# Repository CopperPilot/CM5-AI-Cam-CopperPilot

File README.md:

# CM5 AI Camera Carrier Board: 6-Layer Edge AI Vision Platform

An ultra-compact, high-density, 6-layer carrier board designed for the **Raspberry Pi Compute Module 5 (CM5)**, purpose-built for embedded computer vision, edge AI inference, autonomous robotics, and smart camera applications. Engineered in an exact 55.0 mm × 40.0 mm form factor matching the CM5 module dimensions, the board provides dedicated low-noise power rails, controlled-impedance differential routing (**100 Ω for MIPI and HDMI, 90 Ω for USB**), onboard common-mode filtering, high-speed peripheral multiplexing, and standard 40-pin Raspberry Pi GPIO expansion.

---

## 3D Hardware Presentation

| Top Isometric View | Bottom Mezzanine View |
|:---:|:---:|
|  |  |

| Full System Isometric | Top Routing (F.Cu) |
|:---:|:---:|
|  |  |

---

## System Architecture

```
                    +-------------------------------------------------------+
                    |                      Power Entry                      |
                    | USB-C (Type_C1) w/ 5.1k CC (R2, R3) OR 40-Pin PI1 Header
                    |                             |                         |
                    |               MPS MP1658 3.3V / 3A Buck (U5)          |
                    |                             |                         |
                    |     +-----------------------+-------------------+     |
                    |     |                       |                   |     |
                    | RT9193-2.8V (U1)    RT9193-1.8V (U2)    RT9013-1.2V (U3)
                    +-----+-----------------------+-------------------+-----+
                          |                       |                   |
                     CAM_2V8 Rail            CAM_1V8 Rail        CAM_1V2 Rail
                          |                       |                   |
+-------------------------v-----------------------v-------------------v-----+
|                         Camera Imaging Subsystem                          |
| 30-Pin Sony IMX219 Autofocus Camera Connector (J1)                        |
| 3x 1210 High-Frequency Common-Mode Chokes (L1, L2, L3)                    |
| 2-Lane MIPI CSI-2 (100 Ω Differential, HighSpeed_100R, 0.127 mm Width)    |
+---------------------------------------------+-----------------------------+
                                              |
                          Mezzanine DF40C     | MIPI CSI-2 (100 Ω Diff)
                          Mezzanine DF40C     | (High-Speed Imaging)
+---------------------------------------------v-----------------------------+
|                     Raspberry Pi Compute Module 5 (Module1)               |
| Dual 100-Pin Mezzanine Connectors (Hirose DF40C-100DS-0.4V)                |
| Broadcom BCM2712 Quad-Core Cortex-A76 @ 2.4 GHz, LPDDR4X SDRAM, PCIe 2.0  |
+------+--------------+---------------+---------------+--------------+------+
       | 100 Ω        | 100 Ω         | 90 Ω          | 50 Ω         |
  HDMI | Diff     DSI | Diff      USB | Diff     SDIO | SE      GPIO |
+------v-------+ +----v---------+ +---v---------+ +---v--------+ +---v------+
| Mini-HDMI-C  | | 15-Pin DSI   | | FSUSB42UMX  | | MicroSD    | | 40-Pin   |
| (HDMI1) w/   | | Display FPC  | | Mux (U6) to | | Slot (TF1) | | GPIO     |
| STMPS2171    | | Connector    | | USB-A (J2,  | | w/ Power   | | Header   |
| Switch (U4)  | | (DSI1, 3.3V) | | U8) & USB-C | | Switch(U7) | | (PI1)    |
+--------------+ +--------------+ +-------------+ +------------+ +----------+
```

---

## Reference Design Attribution & Technical Improvements

This design was developed using the architecture and schematic concepts of the **Waveshare CM4 / CM5 Nano Base Board (C)** as an engineering reference. Our team conducted a thorough hardware design review and implemented major electrical, signal integrity, DFM, and manufacturing improvements to deliver a validated, production-ready edge AI camera carrier.

### Summary of Key Engineering Improvements

| Domain | Baseline Reference Limitation | Implemented Engineering Improvement | Benefit / Impact |
|---|---|---|---|
| **Power Regulation** | Faulty feedback divider and mismatched LCSC part (`C25916` 6.49 kΩ) on 3.3V buck regulator `U5` (`MP1658GTF-Z`, `C2960187`); `C21` snubber capacitor assigned 12 pF (`C1547`). | Configured feedback divider with precision 61.9 kΩ ±1% (`R20`, `C25803`) and 20.0 kΩ ±1% (`R21`, `C25765`) resistors for exact **3.305 V** output ($V_{REF}=0.807\text{ V}$); verified 0.1 µF bootstrap (`C24`) and 10 Ω + 330 pF (`R16` + `C21`, `C1534`) SW snubber. | Eliminates catastrophic overvoltage/undervoltage risk on `/PWR_3V3` and damps high-frequency switching ring. |
| **Camera Power & Clock** | `U3` 1.2V camera core LDO assigned a 3.3V LCSC part (`C7434207`); `U1` 2.8V LDO assigned an invalid LCSC code; `C20` on 24 MHz `/MCLK` set to 0.1 µF (`fc = 72.3 kHz`), attenuating the sensor clock. | Assigned verified Richtek LDOs (`U1` 2.8V `C15075`, `U2` 1.8V `C27416`, `U3` 1.2V `C47773`) and restored `C20` to **10 pF (`C32949`)** with `R10 = 22 Ω` (`fc = 723 MHz`). | Protects the 1.2V Sony IMX219 core from 3.3V overvoltage and preserves clean 24 MHz CMOS clock integrity. |
| **Differential Impedance (`100 Ω` vs `90 Ω`)** | Unassigned netclasses in `.kicad_pro` (`netclass_patterns: []`) and documentation conflating MIPI CSI-2, DSI, HDMI TMDS, and USB into a single 90 Ω class with 0.150 mm default trace widths. | Separated and assigned **`HighSpeed_100R` (100 Ω for MIPI CSI-2, MIPI DSI, and HDMI TMDS: `W = 0.127 mm, S = 0.150 mm`)** and **`HighSpeed_90R` (90 Ω for USB 2.0: `W = 0.180 mm, S = 0.150 mm`)** across `.kicad_pro`, `.kicad_pcb`, and `.kicad_dru`. | Matches official Raspberry Pi CM5/CM4, MIPI D-PHY, HDMI 1.4b/2.0 (100 Ω), and USB 2.0 Hi-Speed (90 Ω) specifications on JLCPCB's impedance calculator. |
| **USB Architecture** | Package suffix mismatch on `U6` (`FSUSB42MX` MSOP-10 vs `FSUSB42UMX` UQFN-10) and unverified VBUS switch documentation. | Standardized `U6` to `FSUSB42UMX` (`C11145`, `UQFN-10_1.4x1.8mm_P0.4mm`) with `STMPS2171STR` (`U8`) providing dedicated 5V load switching for USB-A host port `J2`. | Enables reliable USB 2.0 routing between USB-C (`rpiboot` device mode) and vertical USB-A host peripheral port. |
| **Display Connector Parity** | `DSI1` 15-pin FPC connector symbol included legacy unrouted pin `SH` with no matching pad name on footprint `Molex_200528-0150`. | Synchronized `CM5:DSI_15P` symbol with the 15-circuit footprint so `kicad-cli pcb drc --schematic-parity` passes with zero net conflicts. | Eliminates schematic-to-PCB netlist parity errors. |
| **DFM & Custom Rules** | Custom DRC rules in `.kicad_dru` lacked explicit Decision ID traceability and controlled-impedance width constraints. | Annotated all custom rules (`DEC-001` through `DEC-005`) and added explicit `HighSpeed_100R_Impedance_Width` (`0.127 mm`) and `HighSpeed_90R_Impedance_Width` (`0.180 mm`) DRC constraints. | Enforces trace width and clearance compliance automatically during `kicad-cli pcb drc`. |
| **Turnkey PCBA Sourcing** | DNP strap resistors (`R31`, `R32`, `R33` for `WL_nDisable`, `BT_nDisable`, `USB_OTG_ID`) erroneously included in BOM/CPL; mismatched LCSC codes on `HDMI1` and `L1–L3`. | Excluded DNP straps `R31–R33` (`--exclude-dnp`) so Wi-Fi/Bluetooth stay enabled; assigned verified LCSC parts for `HDMI1` (`C424662`) and 1.2×1.0 mm chokes `L1–L3` (`C110443`); consolidated `0.1uF` (`C1525`) BOM rows. | Ready for automated turnkey fabrication and double-sided SMT assembly (87 populated parts across 42 BOM lines). |
| **Automated Testing** | No automated verification of differential netclasses, controlled-impedance trace widths, or critical BOM LCSC mappings. | Expanded the automated PyTest verification suite (`tests/test_pcb.py`) to **29 assertion tests** alongside the 11-stage acceptance runner (`review/verify.sh`). | Continuously verifies physical dimensions, stackup, `100 Ω` / `90 Ω` differential netclasses and trace widths, DRC/ERC parity, and BOM/CPL integrity. |

---

## Hardware Specifications

- **Form Factor & Dimensions:** 55.0 mm × 40.0 mm matching the Raspberry Pi Compute Module mechanical standard, with 3.0 mm corner radii.
- **Compute Module Mezzanine:** Dual Hirose DF40C-100DS-0.4V(51) 100-pin connectors (`Module1`, `C597931`) with 0.40 mm pitch providing high-speed interconnects for MIPI CSI-2, MIPI DSI, HDMI TMDS, USB 2.0, SDIO, and GPIO.
- **Power Subsystem:**
  - **Main Input:** 5.0 V DC via USB Type-C receptacle (`Type_C1`, GCT USB4105-GF-A, `C3020560`) or via 40-pin GPIO expansion header (`PI1`). Recommended power supply: 5V / 3A minimum.
  - **Type-C Configuration:** Dual 5.1 kΩ ±1% CC pull-down resistors (`R2`, `R3`, `C25905`) for standard 5V/3A USB Type-C source negotiation.
  - **3.3 V System Rail (`/PWR_3V3`):** Monolithic Power Systems `MP1658GTF-Z` synchronous buck converter (`U5`, SOT-563, `C2960187`) delivering up to 3.0 A continuous output current (`R20 = 61.9 kΩ C25803`, `R21 = 20.0 kΩ C25765` for 3.305 V nominal output), filtered by a 4.7 µH shielded power inductor (`L7`, `C840574`) and dual 22 µF 0805 ceramic output capacitors (`C25`, `C26`).
  - **Low-Noise Camera Power Tree:**
    - `CAM_2V8` (`/2V8`): 2.8 V analog rail via Richtek `RT9193-28GB` LDO (`U1`, `C15075`) with ferrite bead input filter (`FB1`, 120 Ω `C50843`).
    - `CAM_1V8` (`/1V8`): 1.8 V digital I/O and oscillator rail via Richtek `RT9193-18GB` LDO (`U2`, `C27416`).
    - `CAM_1V2` (`/1V2`): 1.2 V core logic rail via Richtek `RT9013-12` LDO (`U3`, `C47773`).
- **Camera Imaging Subsystem:**
  - 30-pin 0.4 mm pitch board-to-board / FPC receptacle (`J1`, Hirose `DF37NB-30DS-0.4V(75)`, `C6539772`) designed for Sony IMX219-D160 camera modules.
  - Three 1.2 × 1.0 mm 90 Ω common-mode chokes (`L1`, `L2`, `L3`, `MCF1210BF2-900T01`, `C110443`) placed on MIPI CSI-2 clock and data lanes for high-frequency common-mode noise suppression.
  - Controlled **100 Ω differential impedance** (`HighSpeed_100R`, `W = 0.127 mm, S = 0.150 mm`) on MIPI CSI-2 lanes (`/CAM0_*` and `/CSI_*`).
  - 24.0 MHz CMOS crystal oscillator (`X1`, 3.2 × 2.5 mm, `C717686`) with 22 Ω series damping resistor (`R10`) and 10 pF edge-rate filter capacitor (`C20`, `C32949`, $f_c = 723\text{ MHz}$).
- **Video & Display Interfaces:**
  - **Mini-HDMI Type-C:** Molex 47151-0001 connector (`HDMI1`, `C424662`) with dedicated 5 V power distribution switch (`U4`, `STMPS2171STR`, `C157437`), hot-plug detection, and controlled **100 Ω differential impedance** (`HighSpeed_100R`, `W = 0.127 mm, S = 0.150 mm`) on TMDS clock and data pairs (`/HDMI0_CLK_P/N`, `/HDMI0_TX0..2_P/N`).
  - **MIPI DSI Display:** 15-pin 1.0 mm pitch Molex 200528-0150 horizontal FPC connector (`DSI1`, `C2914074`) powered from `/PWR_3V3` with controlled **100 Ω differential impedance** (`HighSpeed_100R`, `W = 0.127 mm, S = 0.150 mm`) on DSI clock and data lanes (`/DSI1_CLK_P/N`, `/DSI1_D0..1_P/N`).
- **Storage & USB Communication:**
  - **MicroSD Card:** Push-push MicroSD card socket (`TF1`, `C91145`) with dedicated `STMPS2171STR` 3.3 V load switch (`U7`, `C157437`) controlled by `/SD_PWREN`.
  - **USB 2.0 Architecture:** Vertical USB 2.0 Type-A host port (`J2`, Molex 67298-4090, `C698207`) with `STMPS2171STR` 5 V VBUS switch (`U8`, `C157437`) and USB Type-C peripheral port (`Type_C1`) multiplexed through an onsemi `FSUSB42UMX` high-speed USB 2.0 switch (`U6`, `C11145`), routed at controlled **90 Ω differential impedance** (`HighSpeed_90R`, `W = 0.180 mm, S = 0.150 mm`).
- **User Interface & Indicators:**
  - Tactile user push-button (`Key1`, `C318884`) connected to `GPIO21` with a 10 kΩ pull-up (`R11`) to `/PWR_3V3`.
  - Status LEDs: 0603 Red 3.3V Power LED (`L5`, `C2286`) and Green Activity LED (`L6`, `C72043`).

---

## Getting Started & Operating Guide

### 1. Mounting the Compute Module 5
1. Align the Compute Module 5 over the dual Hirose DF40C mezzanine connectors (`Module1`) on the bottom side (`B.Cu`).
2. Gently apply uniform downward pressure across the connectors until both 100-pin receptacles click firmly into place.

### 2. Powering the Carrier Board
- **Primary Power (USB-C):** Connect a regulated 5.0 V / 3.0 A USB-C power supply to receptacle `Type_C1`. The onboard CC termination resistors (`R2`, `R3`) negotiate standard 5V operation from USB Power Delivery sources.
- **Alternative Power (GPIO Header):** Connect a regulated 5.0 V DC supply to Pins 2/4 (`5V`) and Pin 6 (`GND`) of the 40-pin header (`PI1`). Do not connect an external 5V supply to `PI1` simultaneously with a host PC on `Type_C1`.
- **Power Indicator:** The onboard red LED (`L5`) illuminates immediately when the regulated 3.3V system rail (`/PWR_3V3`) is active.

### 3. Flashing Compute Module 5 eMMC
For CM5 modules equipped with onboard eMMC:
1. Pull both `/PI_BOOT` (`H4` Pin 1) and `/USB_SEL` (`H4` Pin 3) low to `GND` (`H4` Pin 2) so the BCM2712 processor enters USB `rpiboot` mode and the `FSUSB42UMX` multiplexer (`U6`) selects the USB Type-C port (`Type_C1`).
2. Connect the carrier board to a host PC using the USB Type-C port (`Type_C1`) and run `rpiboot`:
   ```bash
   rpiboot
   ```
3. The CM5 eMMC storage will mount as a mass-storage device on your computer for OS imaging.

### 4. Camera Configuration (Sony IMX219 / MIPI CSI-2)
1. Attach the 30-pin Sony IMX219-D160 camera module to connector `J1`.
2. In Raspberry Pi OS, configure the camera overlay by editing `/boot/firmware/config.txt`:
   ```ini
   # Enable Sony IMX219 Camera Sensor
   dtoverlay=imx219
   ```
3. Reboot and verify camera enumeration using `rpicam-apps`:
   ```bash
   rpicam-hello --list-cameras
   rpicam-hello -t 5000
   ```

### 5. Display Configuration
- **Mini-HDMI (`HDMI1`):** Plug a standard Mini-HDMI to HDMI cable into `HDMI1`. Video output is automatically detected via EDID / HPD.
- **MIPI DSI Display (`DSI1`):** Connect a 15-pin 1.0 mm pitch DSI display ribbon cable to `DSI1` and enable the matching DSI overlay in `/boot/firmware/config.txt` (e.g., `dtoverlay=vc4-kms-dsi-7inch`).

### 6. User Button & GPIO Header
- The tactile push-button (`Key1`) is wired to `GPIO21` with a 10 kΩ pull-up (`R11`) to `/PWR_3V3`. Pressing the button pulls `GPIO21` low.
- The 40-pin GPIO header (`PI1`) follows the standard Raspberry Pi 40-pin pinout.

---

## 6-Layer PCB Stackup & Impedance Control

The board `.kicad_pcb` stackup is synchronized with the **JLCPCB JLC06161H-7628** 6-layer controlled-impedance stackup (1.6 mm nominal thickness, with cross-compatibility verified against **JLC06161H-3313**):

| Layer | Type | Copper Weight | Thickness | Physical Allocation in `.kicad_pcb` |
|---|---|:---:|:---:|---|
| **1. F.Cu** | Signal | 1.0 oz (35 µm) | 0.0350 mm | Top SMT components, high-speed microstrip escapes, camera chokes (`L1–L3`), buck converter (`U5`) |
| *Dielectric 1* | Prepreg (7628) | — | 0.2104 mm | FR-4 ($\varepsilon_r = 4.6$; `0.0994 mm` $\varepsilon_r = 4.05$ on `JLC06161H-3313`) |
| **2. In1.Cu** | Plane / Signal | 0.5 oz (15.2 µm) | 0.0152 mm | Primary `GND` reference plane (`zone GND`) and inner escape routing |
| *Dielectric 2* | Core | — | 0.4000 mm | FR-4 Core ($\varepsilon_r = 4.6$; `0.5500 mm` on `JLC06161H-3313`) |
| **3. In2.Cu** | Signal | 0.5 oz (15.2 µm) | 0.0152 mm | Inner high-speed signal routing (`HDMI0`, `DSI1`, peripheral signals) |
| *Dielectric 3* | Prepreg (7628) | — | 0.2104 mm | FR-4 ($\varepsilon_r = 4.6$; `0.0994 mm` $\varepsilon_r = 4.05$ on `JLC06161H-3313`) |
| **4. In3.Cu** | Power / Signal | 0.5 oz (15.2 µm) | 0.0152 mm | Internal power distribution zones (`/PWR_3V3`, `/CM5_5V`) and inner signal routing |
| *Dielectric 4* | Core | — | 0.4000 mm | FR-4 Core ($\varepsilon_r = 4.6$; `0.5500 mm` on `JLC06161H-3313`) |
| **5. In4.Cu** | Plane / Signal | 0.5 oz (15.2 µm) | 0.0152 mm | Secondary `GND` reference plane (`zone GND`) and high-speed routing |
| *Dielectric 5* | Prepreg (7628) | — | 0.2104 mm | FR-4 ($\varepsilon_r = 4.6$; `0.0994 mm` $\varepsilon_r = 4.05$ on `JLC06161H-3313`) |
| **6. B.Cu** | Signal | 1.0 oz (35 µm) | 0.0350 mm | Bottom mezzanine (`Module1`), camera LDOs (`U1–U3`), USB mux (`U6`), power switches (`U4, U7, U8`) |

### Controlled Impedance Targets (**100 Ω for MIPI and HDMI, 90 Ω for USB**)

The project `.kicad_pro` and `.kicad_dru` files separate differential pairs into two dedicated controlled-impedance netclasses verified against JLCPCB's controlled-impedance models:

| Netclass (`CM5-AI-Cam-CopperPilot.kicad_pro`) | Target Impedance | Assigned Interfaces & Nets | Routed Trace Width ($W$) | Differential Gap ($S$) | Calculated $Z_{\text{diff}}$ / $Z_0$ (`JLC06161H-7628` Stripline) | Calculated $Z_{\text{diff}}$ / $Z_0$ (`JLC06161H-3313` Microstrip) |
|---|:---:|---|:---:|:---:|:---:|:---:|
| **`HighSpeed_100R`** | **100 Ω ±10% Diff** | **MIPI CSI-2** (`/CAM0_*`, `/CSI_*`), **MIPI DSI** (`/DSI1_*`), **HDMI TMDS** (`/HDMI0_CLK_*`, `/HDMI0_TX*`) | **0.127 mm** (5.0 mil) | **0.150 mm** (5.9 mil) | **100.1 Ω** | **98.3 Ω** |
| **`HighSpeed_90R`** | **90 Ω ±10% Diff** | **USB 2.0 Hi-Speed** (`/USB0_P/N`, `/USB0_B_P/N`, `/USBB_P/N`, `/USBD0_P/N`) | **0.180 mm** (7.1 mil) | **0.150 mm** (5.9 mil) | **89.6 Ω** | **88.7 Ω** |
| **Single-Ended Clocks / SDIO** | **50 Ω ±10% SE** | **Camera & SDIO Clocks** (`/MCLK`, `/X1_OUT`, `/SD_CLK`, `/SD_CMD`, `/SD_DAT0..3`) | **0.180 mm** (7.1 mil) | — | **53.7 Ω** | **47.0 Ω** |
| **`Power`** | Low-Z Distribution | `/CM5_5V`, `/PWR_3V3`, `/CM5_3V3`, `/CM5_1V8`, `/HDMI_5V`, `/USB_5V`, `/SD_3.3V`, `/2V8`, `/1V8`, `/1V2` | **0.150–0.500 mm** (0.35 mm nom) | — | — | — |
| **`Default`** | General I/O | GPIO, I2C, control and status signals | **0.150 mm** | — | — | — |

- **Manufacturing Margins:** Global minimum trace width 0.090 mm (routed minimum 0.127 mm on `HighSpeed_100R`), minimum global clearance 0.095 mm, via drill 0.20 mm / pad 0.40 mm (hole-to-hole spacing ≥ 0.254 mm, with local 0.070 mm via-to-via pad clearance rule `DEC-003` under the 0.40 mm pitch Hirose DF40 mezzanine).

---

## Repository Structure

```
.
├── Makefile                        # Unified build orchestrator (test, lint, drc, erc, fab)
├── .gitignore                      # Clean Git exclusion specification
├── LICENSE                         # CERN Open Hardware Licence v2 - Strongly Reciprocal
├── README.md                       # Comprehensive hardware specifications & documentation
├── CM5-AI-Cam-CopperPilot.kicad_pro# KiCad 10 project definition & 100R/90R net classes
├── CM5-AI-Cam-CopperPilot.kicad_sch# Complete multi-block schematic capture
├── CM5-AI-Cam-CopperPilot.kicad_pcb# 6-layer PCB layout (100% routed, 0 DRC violations)
├── CM5-AI-Cam-CopperPilot.kicad_dru# Custom design rules & impedance width constraints
├── CM5.kicad_sym                   # Project-local schematic symbol library
├── sym-lib-table                   # Project symbol library registry (${KIPRJMOD})
├── fp-lib-table                    # Project footprint library registry (${KIPRJMOD})
├── CM5.pretty/                     # Self-contained project-local footprint library
├── CM5.3dshapes/                   # 3D mechanical models (STEP/WRL)
├── 3dmodels/                       # Mezzanine reference CAD models
├── docs/                           # Documentation assets and renders
│   └── images/                     # 3D renders, layer graphics, and mechanical diagrams
├── tests/                          # Automated 29-point PyTest hardware verification suite
│   ├── conftest.py                 # S-expression AST parsers & KiCad CLI fixtures
│   └── test_pcb.py                 # 29 automated hardware assertion tests
├── review/                         # Formal review deliverable & visual diff collateral
│   ├── index.html                  # Interactive visual review report & issue cards
│   ├── verify.sh                   # Automated acceptance test runner (T1 - T11)
│   ├── issues.json                 # Machine-readable issue register (all verified)
│   ├── DECISIONS.md                # Engineering decision records & trade-offs
│   ├── SURVEY.md                   # Systematic schematic & PCB survey report
│   ├── READINESS.md                # Release readiness sign-off checklist
│   └── renders/                    # Baseline, final, and differential layer renders
└── jlcpcb_production/              # JLCPCB manufacturing release bundle
    ├── gerbers_jlcpcb.zip          # Production-ready RS-274X Gerbers and NC drill files
    ├── assembly/
    │   ├── bom_jlcpcb.csv          # Assembled BOM (42 lines, 100% verified LCSC parts, DNP excluded)
    │   └── cpl_jlcpcb.csv          # Pick-and-place centroid coordinates & rotations (DNP excluded)
    ├── gerbers/                    # Uncompressed Gerber and Excellon drill layers
    └── netlist/                    # IPC-D-356 electrical test netlist
```

---

## Automated Verification & Testing

The repository includes a multi-tiered test infrastructure running both unit-level hardware property assertions and full-design acceptance validations.

### Quick Start: Verification Commands

```bash
# Run the complete test and linting pipeline
make all

# Run the 29-point automated PyTest hardware test suite
make test

# Run KiCad Electrical Rule Check (ERC) and Design Rule Check (DRC)
make erc
make drc

# Run the full 11-stage hardware acceptance test runner
make verify

# Rebuild the interactive visual review report
make report

# Generate and package production Gerbers, drill files, BOM, and CPL
make fab
```

### 29-Point PyTest Hardware Test Matrix (`tests/test_pcb.py`)

| Test Group | Test Case | Target / Specification | Result |
|---|---|---|:---:|
| **Board Physical** | `test_board_dimensions` | 55.0 mm × 40.0 mm (±0.5 mm tolerance) | **PASS** |
| | `test_board_outline_closed` | Continuous closed `Edge.Cuts` boundary with rounded corners | **PASS** |
| | `test_layer_stackup_6layer` | 6 copper layers (`F.Cu`, `In1-4.Cu`, `B.Cu`) with `JLC06161H-7628` dielectrics | **PASS** |
| | `test_board_thickness_nominal` | Nominal board thickness of 1.6 mm | **PASS** |
| **Connectivity & Parity** | `test_drc_zero_errors` | KiCad CLI DRC: 0 errors, 0 warnings | **PASS** |
| | `test_drc_zero_unconnected_items` | 100% routed copper (0 unconnected airwires) | **PASS** |
| | `test_drc_schematic_parity` | Zero netlist or component parity mismatches | **PASS** |
| | `test_erc_zero_errors_and_warnings` | KiCad CLI ERC: 0 errors, 0 warnings | **PASS** |
| | `test_power_distribution_nets_present`| `GND`, `5V`, `3V3` power distribution nets verified | **PASS** |
| | `test_camera_subsystem_nets_present` | Dedicated camera rails (`/2V8`, `/1V8`, `/1V2`) & MIPI CSI-2 nets verified | **PASS** |
| | `test_usb_differential_nets_present` | High-speed USB differential pairs verified | **PASS** |
| **Impedance, Trace Geometry & DFM** | `test_differential_netclasses_configured` | `HighSpeed_100R` (100 Ω MIPI/HDMI) and `HighSpeed_90R` (90 Ω USB) assigned in `.kicad_pro` | **PASS** |
| | `test_mipi_hdmi_100ohm_trace_widths` | All 26 MIPI CSI-2, DSI, and HDMI differential nets routed at `0.127 mm` (`100 Ω`) | **PASS** |
| | `test_usb_90ohm_trace_widths` | All 8 USB 2.0 differential nets routed at `0.180 mm` (`90 Ω`) | **PASS** |
| | `test_signal_trace_min_width` | Trace width ≥ 0.09 mm (JLCPCB 6-layer capability) | **PASS** |
| | `test_power_trace_widths` | Power trace width ≥ 0.15 mm (low impedance) | **PASS** |
| | `test_via_drill_and_pad_dimensions` | Via drill ≥ 0.20 mm, pad diameter ≥ 0.40 mm | **PASS** |
| | `test_via_annular_rings` | Via annular rings ≥ 0.10 mm | **PASS** |
| **Subsystem Circuits** | `test_cm5_module_footprint_present` | Hirose DF40 100-pin mezzanine footprint verified | **PASS** |
| | `test_camera_subsystem_chokes` | Common-mode chokes L1, L2, L3 populated (`C110443`) | **PASS** |
| | `test_camera_ldos_present` | Dedicated camera LDOs U1 (`C15075`), U2 (`C27416`), U3 (`C47773`) populated | **PASS** |
| | `test_buck_regulator_present` | MP1658 3.3V/3A synchronous buck regulator U5 populated (`C2960187`) | **PASS** |
| | `test_usb_c_cc_termination_resistors`| 5.1 kΩ pull-down resistors R2, R3 on CC pins | **PASS** |
| | `test_peripherals_present` | Connectors HDMI1, DSI1, TF1, PI1, Type_C1, J2 verified | **PASS** |
| **Repo Hygiene & DFM** | `test_no_absolute_user_paths_in_tables` | Zero user machine path leaks; 100% relative `${KIPRJMOD}` paths | **PASS** |
| | `test_manufacturing_bom_completeness` | BOM complete with 100% verified LCSC part numbers | **PASS** |
| | `test_critical_bom_lcsc_and_dnp_exclusion` | Verified LCSC codes on `R20, U1, U3, U5, U6, HDMI1, L1–L3, C20, C21` & DNP exclusion of `R31–R33` | **PASS** |
| | `test_manufacturing_cpl_completeness` | CPL centroid coordinates, rotations, and DNP exclusion verified | **PASS** |
| | `test_gerber_package_files` | All 6 copper layers, mask, silk, paste, and drill files present | **PASS** |

---

## Interactive Visual Review Deliverable

An interactive, self-contained HTML review deliverable is available at [`review/index.html`](review/index.html).

Key features of the report:
- **Zero Unexplained Changes:** Every modified region on every sheet and layer maps to a tracked issue ID.
- **Layer-by-Layer Visual Diff Viewer:** Interactive comparison between baseline and release candidate for all 6 copper layers, silkscreens, solder masks, and schematic.
- **Detailed Issue Cards:** Tracked and verified issues with side-by-side Before/After/Diff image crops, engineering rationales, and git commit references.
- **Full Parity & Acceptance Scoreboard:** Live compliance status across tests T1 through T11.

---

## Manufacturing & Ordering Guide (JLCPCB)

To order fabricated and assembled boards directly from JLCPCB:

1. **PCB Fabrication:**
   - Upload `jlcpcb_production/gerbers_jlcpcb.zip`.
   - **Dimensions:** 55.0 mm × 40.0 mm.
   - **Layer Count:** 6 Layers.
   - **Impedance Control:** Yes — Select Stackup **JLC06161H-7628** (**100 Ω diff for MIPI CSI-2, DSI, and HDMI; 90 Ω diff for USB 2.0**).
   - **Surface Finish:** ENIG (Electroless Nickel Immersion Gold) recommended for high-density 0.4 mm pitch mezzanine pads.
   - **Copper Weight:** 1 oz outer / 0.5 oz inner.
   - **Solder Mask / Silkscreen:** Green mask / White silkscreen (or color of choice).
2. **SMT Assembly (PCBA):**
   - **Assembly Type:** Standard PCBA.
   - **Assembly Side:** Top and Bottom.
   - **BOM File:** Upload `jlcpcb_production/assembly/bom_jlcpcb.csv`.
   - **CPL / Centroid File:** Upload `jlcpcb_production/assembly/cpl_jlcpcb.csv`.
3. **Complete Order Spec:** Refer to [`manufacturing/ORDER_SPEC.md`](manufacturing/ORDER_SPEC.md) for full order form field values.

---

## License

This project is licensed under the **CERN Open Hardware Licence Version 2 - Strongly Reciprocal** ([CERN-OHL-S-2.0](LICENSE)).

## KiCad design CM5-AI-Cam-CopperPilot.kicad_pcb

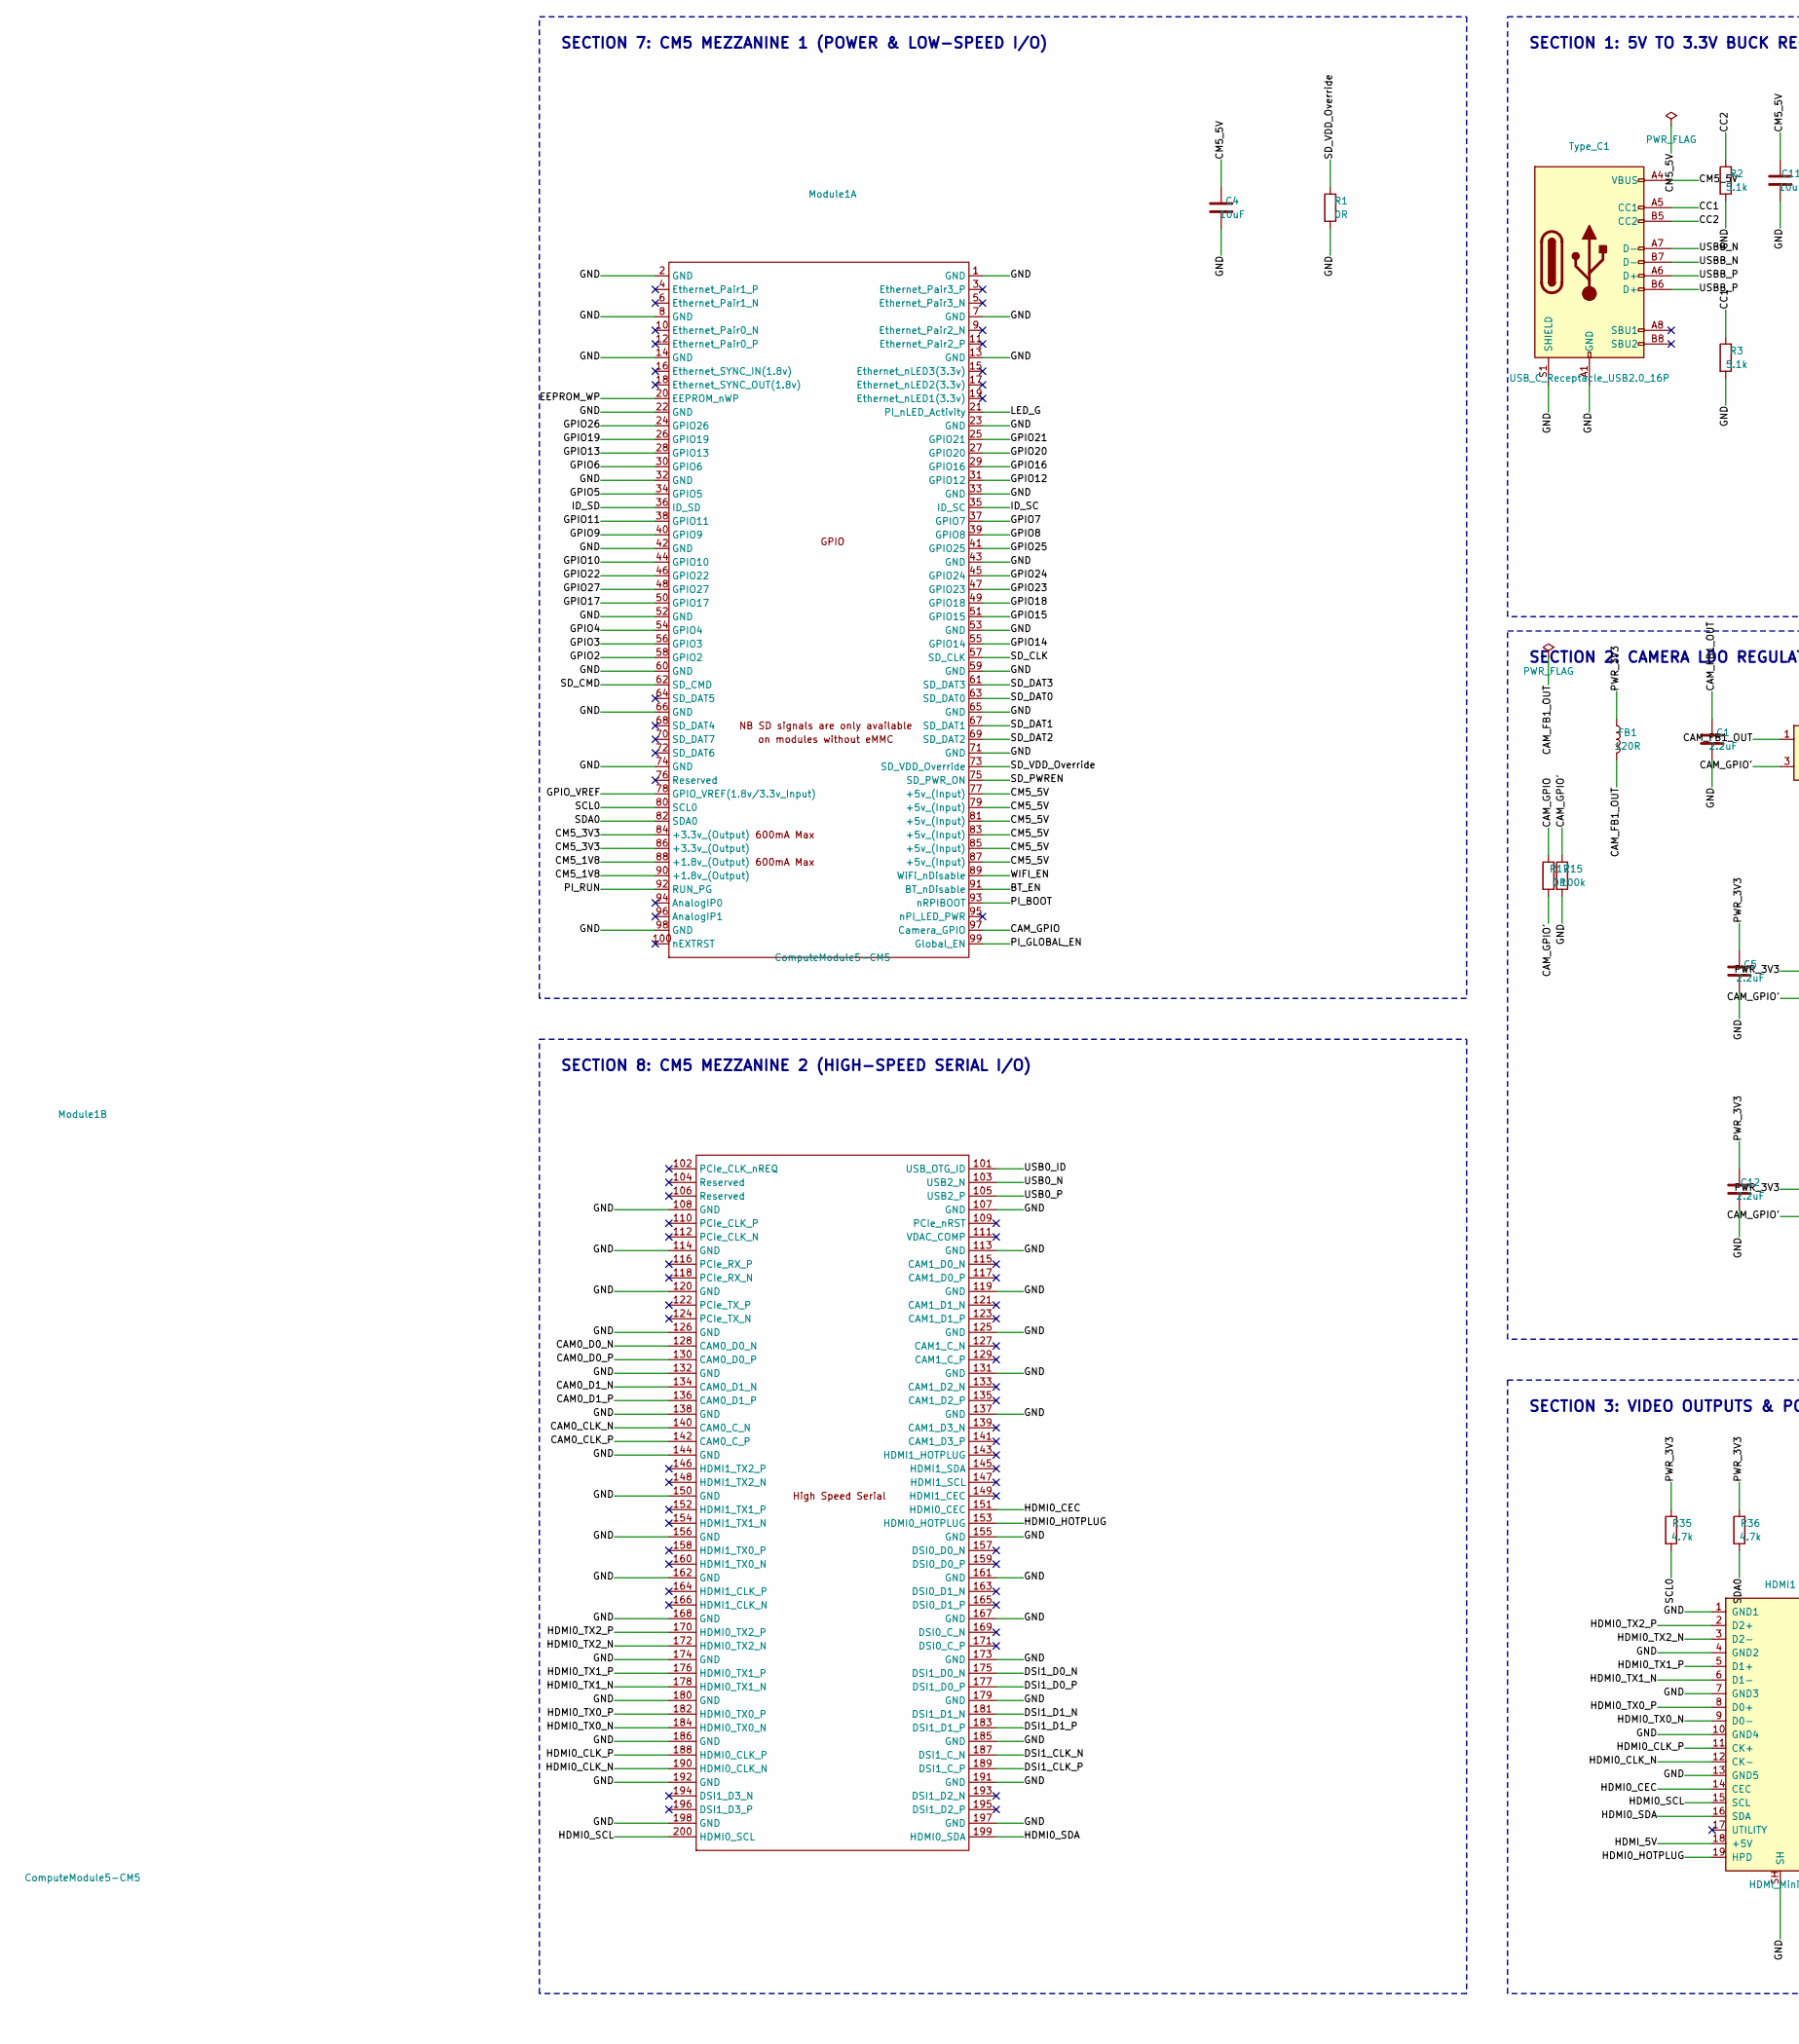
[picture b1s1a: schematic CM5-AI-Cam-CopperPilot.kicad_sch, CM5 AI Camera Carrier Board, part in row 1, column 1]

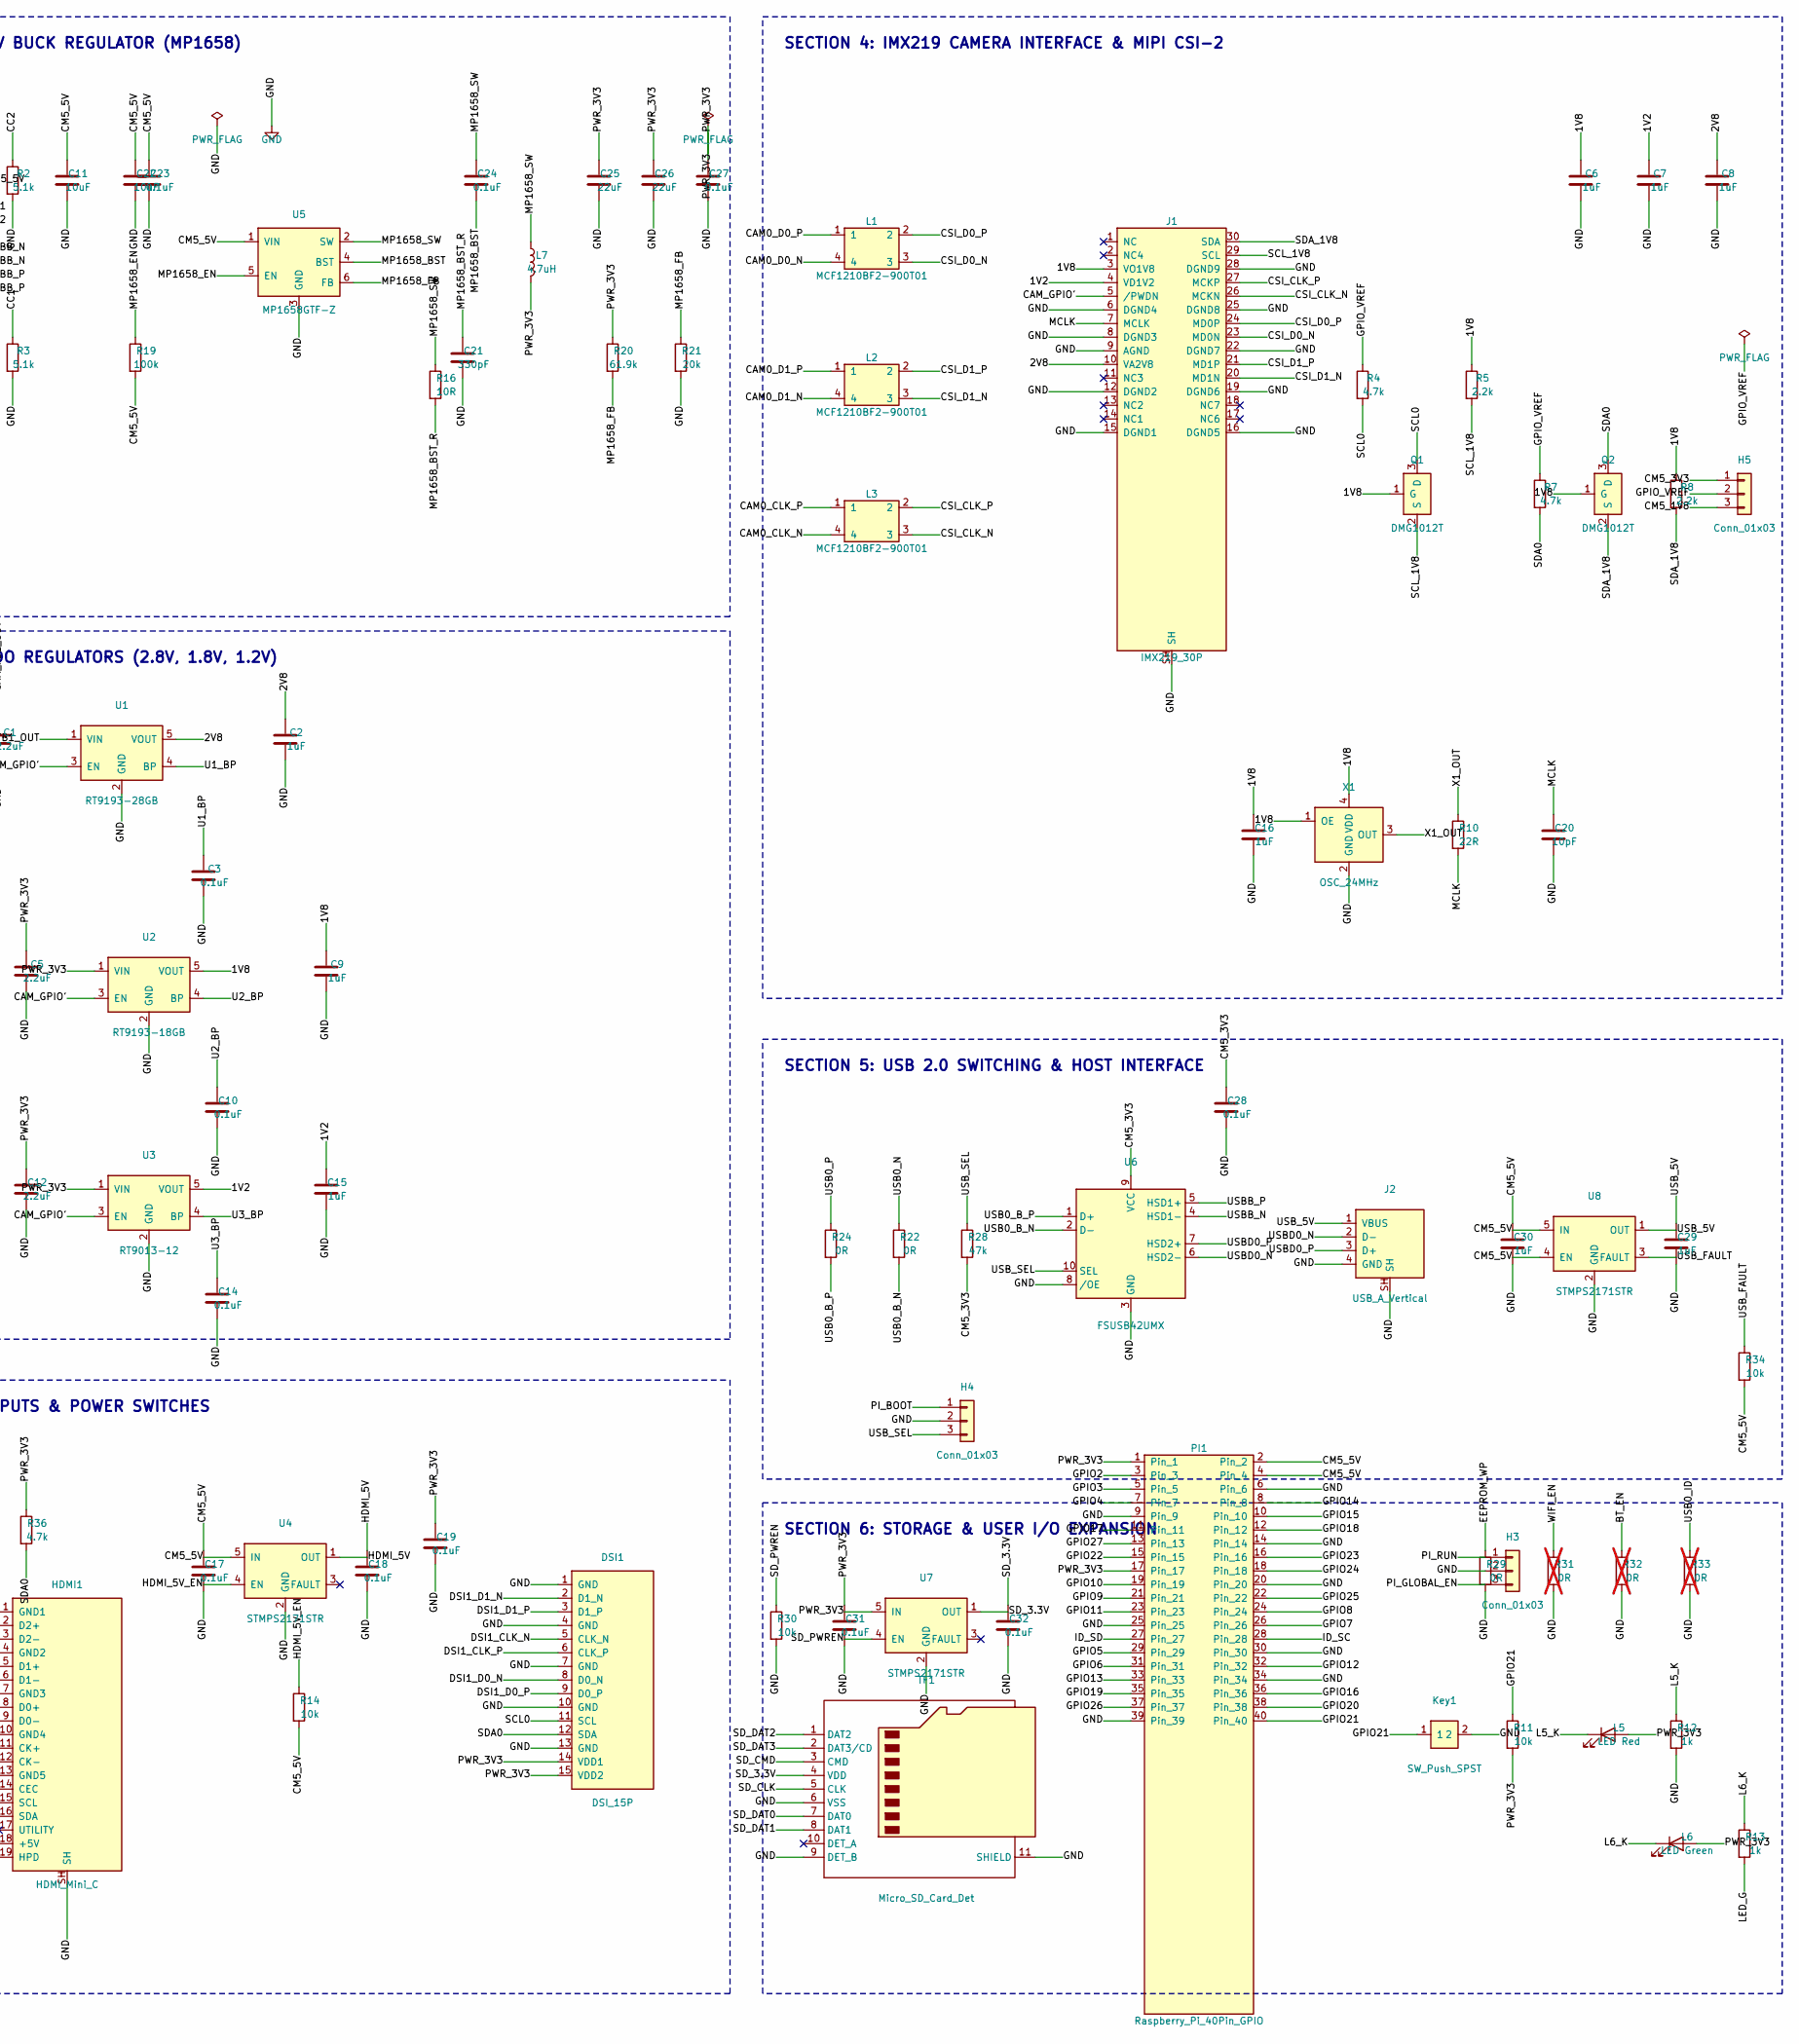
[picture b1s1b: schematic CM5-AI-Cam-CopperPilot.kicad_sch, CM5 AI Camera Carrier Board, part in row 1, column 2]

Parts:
C1, C5, C12: 2.2uF; C_0402_1005Metric; LCSC C23733
C2, C6, C7, C8, C9, C15, C16, C29, C30: 1uF; C_0402_1005Metric; LCSC C52923
C3, C10, C14, C17, C18, C19, C23, C24, C27, C28, C31, C32: 0.1uF; C_0402_1005Metric; LCSC C1525
C4, C11, C22: 10uF; C_0805_2012Metric; LCSC C15850
C20: 10pF; C_0402_1005Metric; LCSC C32949
C21: 330pF; C_0402_1005Metric; LCSC C1534
C25, C26: 22uF; C_0805_2012Metric; LCSC C45783
DSI1: DSI_15P; Molex_200528-0150_1x15-1MP_P1.00mm_Horizontal; LCSC C2914074
FB1: 120R; R_0603_1608Metric; LCSC C50843
H3, H4, H5: Conn_01x03; PinHeader_1x03_P2.54mm_Vertical; LCSC C49257
HDMI1: HDMI_Mini_C; HDMI_Mini-C_Molex_47151-0001; LCSC C424662
J1: IMX219_30P; Camera_Module_IMX219-D160; LCSC C6539772
J2: USB_A_Vertical; MOLEX_USB_67298-4090; LCSC C698207
Key1: SW_Push_SPST; SW_SPST_PTS645Sx43SMTR92; LCSC C318884
L1, L2, L3: MCF1210BF2-900T01; L_CommonModeChoke_Coilank_ACM1210; LCSC C110443
L5: LED Red; LED_0603_1608Metric; LCSC C2286
L6: LED Green; LED_0603_1608Metric; LCSC C72043
L7: 4.7uH; L_Bourns_SRP5030CC; LCSC C840574
Module1: ComputeModule5-CM5; Raspberry-Pi-5-Compute-Module; LCSC C597931
PI1: Raspberry_Pi_40Pin_GPIO; PinHeader_2x20_P2.54mm_Vertical; LCSC C50980
Q1, Q2: DMG1012T; SOT-523; LCSC C20512
R1, R17, R22, R24, R29: 0R; R_0402_1005Metric; LCSC C17168
R2, R3: 5.1k; R_0402_1005Metric; LCSC C25905
R4, R7, R35, R36: 4.7k; R_0402_1005Metric; LCSC C25900
R5, R8: 2.2k; R_0402_1005Metric; LCSC C25879
R10: 22R; R_0402_1005Metric; LCSC C25092
R11, R14, R30, R34: 10k; R_0402_1005Metric; LCSC C25744
R12, R13: 1k; R_0402_1005Metric; LCSC C11702
R15, R19: 100k; R_0402_1005Metric; LCSC C25741
R16: 10R; R_0402_1005Metric; LCSC C25077
R20: 61.9k; R_0402_1005Metric; LCSC C25803
R21: 20k; R_0402_1005Metric; LCSC C25765
R28: 47k; R_0402_1005Metric; LCSC C25792
R31, R32, R33: 0R; R_0402_1005Metric; LCSC C17168; not fitted
TF1: Micro_SD_Card_Det; SDCARD_MOLEX_503398-1892; LCSC C91145
Type_C1: USB_C_Receptacle_USB2.0_16P; USB_C_Receptacle_GCT_USB4105-xx-A_16P_TopMnt_Horizontal; LCSC C3020560
U1: RT9193-28GB; SOT-23-5; LCSC C15075
U2: RT9193-18GB; SOT-23-5; LCSC C27416
U3: RT9013-12; SOT-23-5; LCSC C47773
U4, U7, U8: STMPS2171STR; SOT-23-5; LCSC C157437
U5: MP1658GTF-Z; SOT-563; LCSC C2960187
U6: FSUSB42UMX; UQFN-10_1.4x1.8mm_P0.4mm; LCSC C11145
X1: OSC_24MHz; Crystal_SMD_3225-4Pin_3.2x2.5mm; LCSC C717686

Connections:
/1V2: C7.1, C15.1, J1.4 (VD1V2), U3.5 (VOUT)
/1V8: C6.1, C9.1, C16.1, J1.3 (VO1V8), Q1.1 (G), Q2.1 (G), R5.1, R8.1, U2.5 (VOUT), X1.1 (OE), X1.4 (VDD)
/2V8: C2.1, C8.1, J1.10 (VA2V8), U1.5 (VOUT)
/BT_EN: Module1.91 (BT_nDisable), R32.1
/CAM0_CLK_N: L3.4, Module1.140 (CAM0_C_N)
/CAM0_CLK_P: L3.1, Module1.142 (CAM0_C_P)
/CAM0_D0_N: L1.4, Module1.128 (CAM0_D0_N)
/CAM0_D0_P: L1.1, Module1.130 (CAM0_D0_P)
/CAM0_D1_N: L2.4, Module1.134 (CAM0_D1_N)
/CAM0_D1_P: L2.1, Module1.136 (CAM0_D1_P)
/CAM_FB1_OUT: C1.1, FB1.2, U1.1 (VIN)
/CAM_GPIO: Module1.97 (Camera_GPIO), R17.1
/CAM_GPIO': J1.5 (/PWDN), R15.1, R17.2, U1.3 (EN), U2.3 (EN), U3.3 (EN)
/CC1: R3.1, Type_C1.A5 (CC1)
/CC2: R2.1, Type_C1.B5 (CC2)
/CM5_1V8: H5.3, Module1.88 (+1.8v_(Output)), Module1.90 (+1.8v_(Output))
/CM5_3V3: C28.1, H5.1, Module1.84 (+3.3v_(Output)), Module1.86 (+3.3v_(Output)), R28.2, U6.9 (VCC)
/CM5_5V: C4.1, C11.1, C17.1, C22.1, C23.1, C30.1, Module1.77 (+5v_(Input)), Module1.79 (+5v_(Input)), Module1.81 (+5v_(Input)), Module1.83 (+5v_(Input)), Module1.85 (+5v_(Input)), Module1.87 (+5v_(Input)), PI1.2, PI1.4, R14.2, R19.2, R34.2, Type_C1.A4 (VBUS), Type_C1.A9 (VBUS), Type_C1.B4 (VBUS), Type_C1.B9 (VBUS), U4.5 (IN), U5.1 (VIN), U8.4 (EN), U8.5 (IN)
/CSI_CLK_N: J1.26 (MCKN), L3.3
/CSI_CLK_P: J1.27 (MCKP), L3.2
/CSI_D0_N: J1.23 (MD0N), L1.3
/CSI_D0_P: J1.24 (MD0P), L1.2
/CSI_D1_N: J1.20 (MD1N), L2.3
/CSI_D1_P: J1.21 (MD1P), L2.2
/DSI1_CLK_N: DSI1.5 (CLK_N), Module1.187 (DSI1_C_N)
/DSI1_CLK_P: DSI1.6 (CLK_P), Module1.189 (DSI1_C_P)
/DSI1_D0_N: DSI1.8 (D0_N), Module1.175 (DSI1_D0_N)
/DSI1_D0_P: DSI1.9 (D0_P), Module1.177 (DSI1_D0_P)
/DSI1_D1_N: DSI1.2 (D1_N), Module1.181 (DSI1_D1_N)
/DSI1_D1_P: DSI1.3 (D1_P), Module1.183 (DSI1_D1_P)
/EEPROM_WP: Module1.20 (EEPROM_nWP), R29.1
/GPIO2: Module1.58 (GPIO2), PI1.3
/GPIO3: Module1.56 (GPIO3), PI1.5
/GPIO4: Module1.54 (GPIO4), PI1.7
/GPIO5: Module1.34 (GPIO5), PI1.29
/GPIO6: Module1.30 (GPIO6), PI1.31
/GPIO7: Module1.37 (GPIO7), PI1.26
/GPIO8: Module1.39 (GPIO8), PI1.24
/GPIO9: Module1.40 (GPIO9), PI1.21
/GPIO10: Module1.44 (GPIO10), PI1.19
/GPIO11: Module1.38 (GPIO11), PI1.23
/GPIO12: Module1.31 (GPIO12), PI1.32
/GPIO13: Module1.28 (GPIO13), PI1.33
/GPIO14: Module1.55 (GPIO14), PI1.8
/GPIO15: Module1.51 (GPIO15), PI1.10
/GPIO16: Module1.29 (GPIO16), PI1.36
/GPIO17: Module1.50 (GPIO17), PI1.11
/GPIO18: Module1.49 (GPIO18), PI1.12
/GPIO19: Module1.26 (GPIO19), PI1.35
/GPIO20: Module1.27 (GPIO20), PI1.38
/GPIO21: Key1.1, Module1.25 (GPIO21), PI1.40, R11.1
/GPIO22: Module1.46 (GPIO22), PI1.15
/GPIO23: Module1.47 (GPIO23), PI1.16
/GPIO24: Module1.45 (GPIO24), PI1.18
/GPIO25: Module1.41 (GPIO25), PI1.22
/GPIO26: Module1.24 (GPIO26), PI1.37
/GPIO27: Module1.48 (GPIO27), PI1.13
/GPIO_VREF: H5.2, Module1.78 (GPIO_VREF(1.8v/3.3v_Input)), R4.1, R7.1
/HDMI0_CEC: HDMI1.14 (CEC), Module1.151 (HDMI0_CEC)
/HDMI0_CLK_N: HDMI1.12 (CK-), Module1.190 (HDMI0_CLK_N)
/HDMI0_CLK_P: HDMI1.11 (CK+), Module1.188 (HDMI0_CLK_P)
/HDMI0_HOTPLUG: HDMI1.19 (HPD), Module1.153 (HDMI0_HOTPLUG)
/HDMI0_SCL: HDMI1.15 (SCL), Module1.200 (HDMI0_SCL)
/HDMI0_SDA: HDMI1.16 (SDA), Module1.199 (HDMI0_SDA)
/HDMI0_TX0_N: HDMI1.9 (D0-), Module1.184 (HDMI0_TX0_N)
/HDMI0_TX0_P: HDMI1.8 (D0+), Module1.182 (HDMI0_TX0_P)
/HDMI0_TX1_N: HDMI1.6 (D1-), Module1.178 (HDMI0_TX1_N)
/HDMI0_TX1_P: HDMI1.5 (D1+), Module1.176 (HDMI0_TX1_P)
/HDMI0_TX2_N: HDMI1.3 (D2-), Module1.172 (HDMI0_TX2_N)
/HDMI0_TX2_P: HDMI1.2 (D2+), Module1.170 (HDMI0_TX2_P)
/HDMI_5V: C18.1, HDMI1.18 (+5V), U4.1 (OUT)
/HDMI_5V_EN: R14.1, U4.4 (EN)
/ID_SC: Module1.35 (ID_SC), PI1.28
/ID_SD: Module1.36 (ID_SD), PI1.27
/L5_K: L5.1 (K), R12.1
/L6_K: L6.1 (K), R13.1
/LED_G: Module1.21 (PI_nLED_Activity), R13.2
/MCLK: C20.1, J1.7 (MCLK), R10.2
/MP1658_BST: C24.2, U5.4 (BST)
/MP1658_BST_R: C21.1, R16.2
/MP1658_EN: R19.1, U5.5 (EN)
/MP1658_FB: R20.2, R21.1, U5.6 (FB)
/MP1658_SW: C24.1, L7.1, R16.1, U5.2 (SW)
/PI_BOOT: H4.1, Module1.93 (nRPIBOOT)
/PI_GLOBAL_EN: H3.3, Module1.99 (Global_EN)
/PI_RUN: H3.1, Module1.92 (RUN_PG)
/PWR_3V3: C5.1, C12.1, C19.1, C25.1, C26.1, C27.1, C31.1, DSI1.14 (VDD1), DSI1.15 (VDD2), FB1.1, L5.2 (A), L6.2 (A), L7.2, PI1.1, PI1.17, R11.2, R20.1, R35.1, R36.1, U2.1 (VIN), U3.1 (VIN), U7.5 (IN)
/SCL0: DSI1.11 (SCL), Module1.80 (SCL0), Q1.3 (D), R4.2, R35.2
/SCL_1V8: J1.29 (SCL), Q1.2 (S), R5.2
/SDA0: DSI1.12 (SDA), Module1.82 (SDA0), Q2.3 (D), R7.2, R36.2
/SDA_1V8: J1.30 (SDA), Q2.2 (S), R8.2
/SD_3.3V: C32.1, TF1.4 (VDD), U7.1 (OUT)
/SD_CLK: Module1.57 (SD_CLK), TF1.5 (CLK)
/SD_CMD: Module1.62 (SD_CMD), TF1.3 (CMD)
/SD_DAT0: Module1.63 (SD_DAT0), TF1.7 (DAT0)
/SD_DAT1: Module1.67 (SD_DAT1), TF1.8 (DAT1)
/SD_DAT2: Module1.69 (SD_DAT2), TF1.1 (DAT2)
/SD_DAT3: Module1.61 (SD_DAT3), TF1.2 (DAT3/CD)
/SD_PWREN: Module1.75 (SD_PWR_ON), R30.1, U7.4 (EN)
/SD_VDD_Override: Module1.73 (SD_VDD_Override), R1.1
/U1_BP: C3.1, U1.4 (BP)
/U2_BP: C10.1, U2.4 (BP)
/U3_BP: C14.1, U3.4 (BP)
/USB0_B_N: R22.2, U6.2 (D-)
/USB0_B_P: R24.2, U6.1 (D+)
/USB0_ID: Module1.101 (USB_OTG_ID), R33.1
/USB0_N: Module1.103 (USB2_N), R22.1
/USB0_P: Module1.105 (USB2_P), R24.1
/USBB_N: Type_C1.A7 (D-), Type_C1.B7 (D-), U6.4 (HSD1-)
/USBB_P: Type_C1.A6 (D+), Type_C1.B6 (D+), U6.5 (HSD1+)
/USBD0_N: J2.2 (D-), U6.6 (HSD2-)
/USBD0_P: J2.3 (D+), U6.7 (HSD2+)
/USB_5V: C29.1, J2.1 (VBUS), U8.1 (OUT)
/USB_FAULT: R34.1, U8.3 (FAULT)
/USB_SEL: H4.3, R28.1, U6.10 (SEL)
/WIFI_EN: Module1.89 (WiFi_nDisable), R31.1
/X1_OUT: R10.1, X1.3 (OUT)
GND: C1.2, C2.2, C3.2, C4.2, C5.2, C6.2, C7.2, C8.2, C9.2, C10.2, C11.2, C12.2, C14.2, C15.2, C16.2, C17.2, C18.2, C19.2, C20.2, C21.2, C22.2, C23.2, C25.2, C26.2, C27.2, C28.2, C29.2, C30.2, C31.2, C32.2, DSI1.1 (GND), DSI1.4 (GND), DSI1.7 (GND), DSI1.10 (GND), DSI1.13 (GND), H3.2, H4.2, HDMI1.1 (GND1), HDMI1.4 (GND2), HDMI1.7 (GND3), HDMI1.10 (GND4), HDMI1.13 (GND5), HDMI1.SH, J1.6 (DGND4), J1.8 (DGND3), J1.9 (AGND), J1.12 (DGND2), J1.15 (DGND1), J1.16 (DGND5), J1.19 (DGND6), J1.22 (DGND7), J1.25 (DGND8), J1.28 (DGND9), J1.SH, J2.4 (GND), J2.SH, Key1.2, Module1.1 (GND), Module1.2 (GND), Module1.7 (GND), Module1.8 (GND), Module1.13 (GND), Module1.14 (GND), Module1.22 (GND), Module1.23 (GND), Module1.32 (GND), Module1.33 (GND), Module1.42 (GND), Module1.43 (GND), Module1.52 (GND), Module1.53 (GND), Module1.59 (GND), Module1.60 (GND), Module1.65 (GND), Module1.66 (GND), Module1.71 (GND), Module1.74 (GND), Module1.98 (GND), Module1.107 (GND), Module1.108 (GND), Module1.113 (GND), Module1.114 (GND), Module1.119 (GND), Module1.120 (GND), Module1.125 (GND), Module1.126 (GND), Module1.131 (GND), Module1.132 (GND), Module1.137 (GND), Module1.138 (GND), Module1.144 (GND), Module1.150 (GND), Module1.155 (GND), Module1.156 (GND), Module1.161 (GND), Module1.162 (GND), Module1.167 (GND), Module1.168 (GND), Module1.173 (GND), Module1.174 (GND), Module1.179 (GND), Module1.180 (GND), Module1.185 (GND), Module1.186 (GND), Module1.191 (GND), Module1.192 (GND), Module1.197 (GND), Module1.198 (GND), PI1.6, PI1.9, PI1.14, PI1.20, PI1.25, PI1.30, PI1.34, PI1.39, R1.2, R2.2, R3.2, R12.2, R15.2, R21.2, R29.2, R30.2, R31.2, R32.2, R33.2, TF1.6 (VSS), TF1.9 (DET_B), TF1.11 (SHIELD), Type_C1.A1 (GND), Type_C1.A12 (GND), Type_C1.B1 (GND), Type_C1.B12 (GND), Type_C1.S1 (SHIELD), U1.2 (GND), U2.2 (GND), U3.2 (GND), U4.2 (GND), U5.3 (GND), U6.3 (GND), U6.8 (/OE), U7.2 (GND), U8.2 (GND), X1.2 (GND)

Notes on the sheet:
SECTION 1: 5V TO 3.3V BUCK REGULATOR (MP1658)
SECTION 2: CAMERA LDO REGULATORS (2.8V, 1.8V, 1.2V)
SECTION 3: VIDEO OUTPUTS & POWER SWITCHES
SECTION 4: IMX219 CAMERA INTERFACE & MIPI CSI-2
SECTION 5: USB 2.0 SWITCHING & HOST INTERFACE
SECTION 6: STORAGE & USER I/O EXPANSION
SECTION 7: CM5 MEZZANINE 1 (POWER & LOW-SPEED I/O)
SECTION 8: CM5 MEZZANINE 2 (HIGH-SPEED SERIAL I/O)

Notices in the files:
README.md:
License: CERN-OHL-S-2.0
